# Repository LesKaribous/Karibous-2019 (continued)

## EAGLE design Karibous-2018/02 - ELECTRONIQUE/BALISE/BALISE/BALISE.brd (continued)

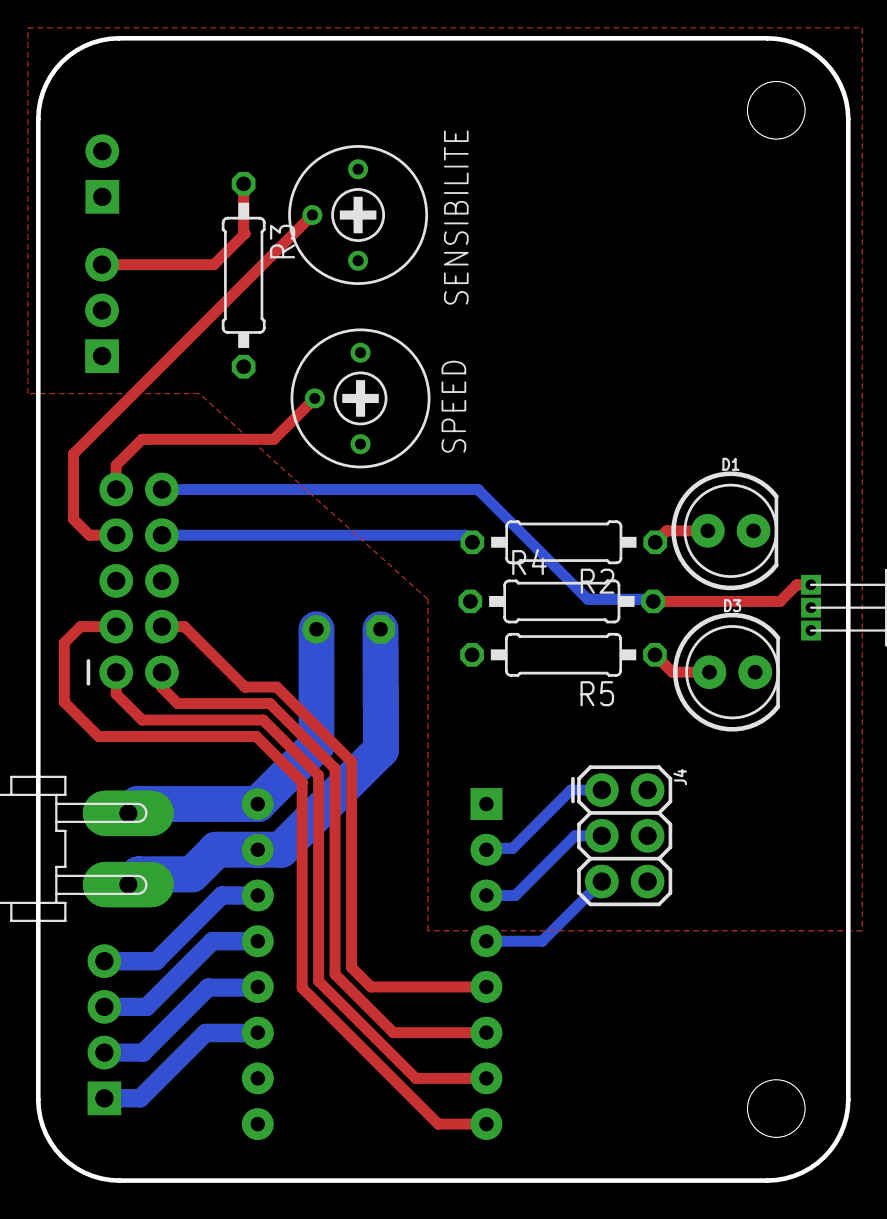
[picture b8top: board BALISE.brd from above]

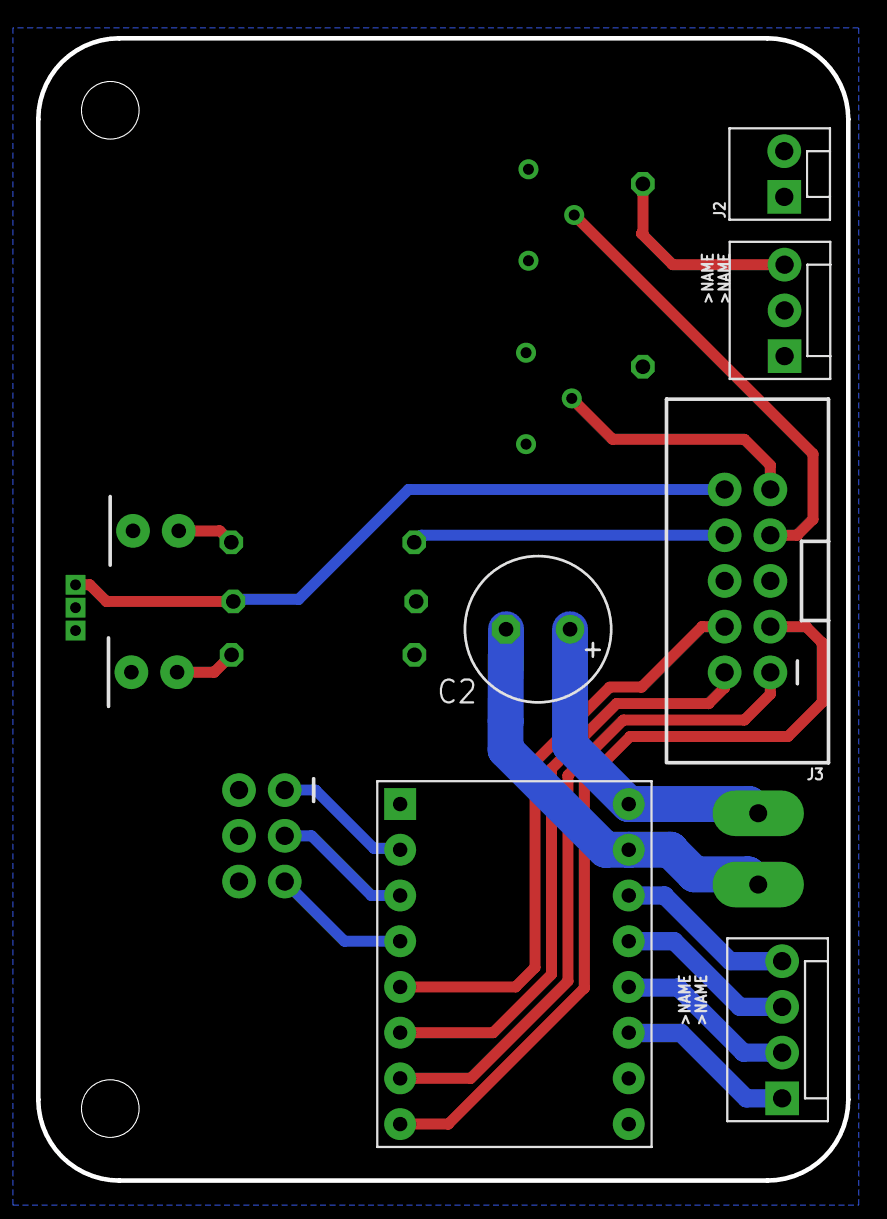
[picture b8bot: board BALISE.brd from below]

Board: 2 copper layers, 45.0 x 63.5 mm, 17 parts (6 on the bottom side), 22 nets.

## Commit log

2018-12-29 update electronique
2018-12-29 comit con
2019-01-12 Modif 2019
2019-03-24 Clean up repo
2019-03-24 MAJ IHM
2019-03-24 Update IHM
2019-05-27 update : nouvelle gestion des robots
2019-05-27 update Ajout de l'experience
2019-08-28 last code
